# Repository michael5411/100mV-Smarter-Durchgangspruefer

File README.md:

# 100mV-Smarter-Durchgangspruefer:
Dieses Gerät testet Durchgang und Widerstände bis 100Ω nur mit 100 mV. Dadurch können Verbindungen und viele Komponenten in eingebautem Zustand gecheckt werden, ohne dass Halbleiterübergänge die Messung verfälschen. Das Messgerät gibt verschiedene Tonfolgen für unterschiedliche Widerstandsbereiche aus. Es ist programmierbar.

Neue Versionen, neue Infos zum Projekt unter: **https://art-of-electronics.blog**

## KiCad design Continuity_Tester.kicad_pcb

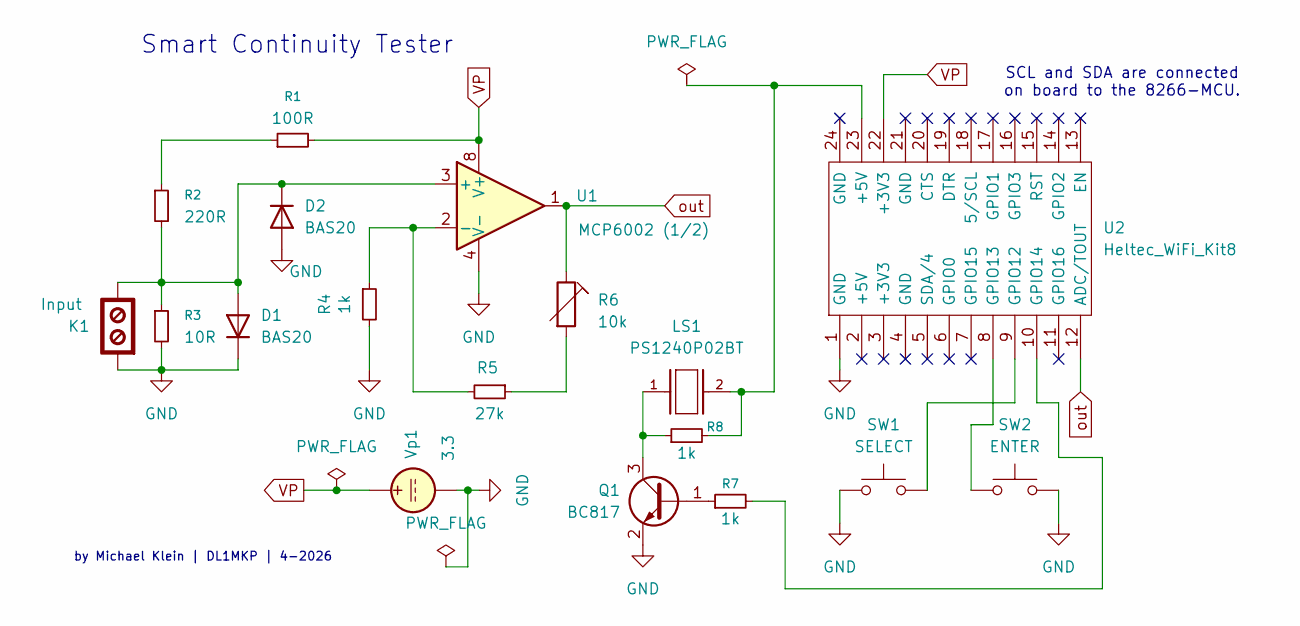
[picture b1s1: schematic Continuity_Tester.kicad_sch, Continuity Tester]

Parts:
D1, D2: BAS20; SOT-23
K1: Input; TerminalBlock_TE_282834-2_1x02_P2.54mm_Horizontal
LS1: PS1240P02BT; XDCR_PS1240P02BT
Q1: BC817; SOT-23
R1: 100R; R_0805_2012Metric_Pad1.20x1.40mm_HandSolder
R2: 220R; R_0805_2012Metric_Pad1.20x1.40mm_HandSolder
R3: 10R; R_0805_2012Metric_Pad1.20x1.40mm_HandSolder
R4, R7, R8: 1k; R_0805_2012Metric_Pad1.20x1.40mm_HandSolder
R5: 27k; R_0805_2012Metric_Pad1.20x1.40mm_HandSolder
R6: 10k; Potentiometer_Bourns_3314G
SW1: SELECT; SW_SPST_B3U-1000P
SW2: ENTER; SW_SPST_B3U-1000P
U1: MCP6002 (1/2); SOP-8_3.76x4.96mm_P1.27mm
U2: Heltec_WiFi_Kit8
Vp1: 3.3

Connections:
GND: D1.3 (K), D2.1 (A), K1.1, Q1.2 (E), R3.2, R4.2, SW1.1, SW2.2, U1.4 (V-), U2.1 (GND), Vp1.2
unnamed: D1.1 (A), D2.3 (K), K1.2, R2.2, R3.1, U1.3 (+)
unnamed: LS1.2, R8.2, U2.23 (+5V)
unnamed: Q1.1 (B), R7.1
unnamed: LS1.1, Q1.3 (C), R8.1
unnamed: R1.1, R2.1
unnamed: R5.1, R6.2
unnamed: R4.1, R5.2, U1.2 (-)
unnamed: SW1.2, U2.9 (GPIO12)
unnamed: SW2.1, U2.8 (GPIO13)
unnamed: R7.2, U2.10 (GPIO14)
VP: R1.2, U1.8 (V+), U2.22 (+3V3), Vp1.1
out: R6.1, U1.1, U2.12 (ADC/TOUT)

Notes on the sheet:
Smart Continuity Tester
by Michael Klein | DL1MKP | 4-2026
SCL and SDA are connected on board to the 8266-MCU.

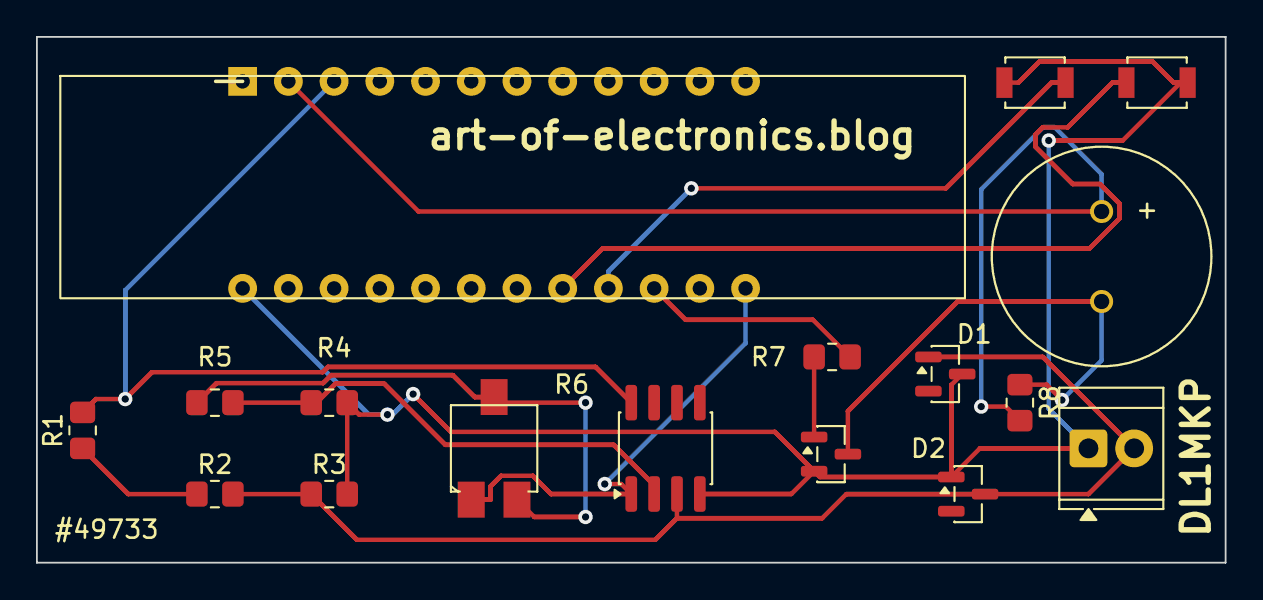
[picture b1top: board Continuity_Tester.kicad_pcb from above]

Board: 2 copper layers, 66.0 x 29.2 mm, 17 parts (0 on the bottom side), 13 nets.

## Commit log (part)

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2026-06-29 KiCad10 Schaltplan
2026-06-29 Sketch für den Heltec WiFi Kit 8
2026-06-29 Detaillierte Projektbeschreibung
    1) Projektbeschreibung
    2) Erklärung des Arduino C++ Codes
    3) Bedienungsanleitung für das Gerät
2026-06-29 Update README with device description and image
2026-06-29 Revise README title and description formatting
    Updated the title format and adjusted wording for clarity.
2026-06-29 Professionelles SMD-board
    Bitte email an: michael (ät) art-of-electronics.blog.
2026-06-29 Revise project info and highlight blog link
    Updated project information and emphasized the blog link.
